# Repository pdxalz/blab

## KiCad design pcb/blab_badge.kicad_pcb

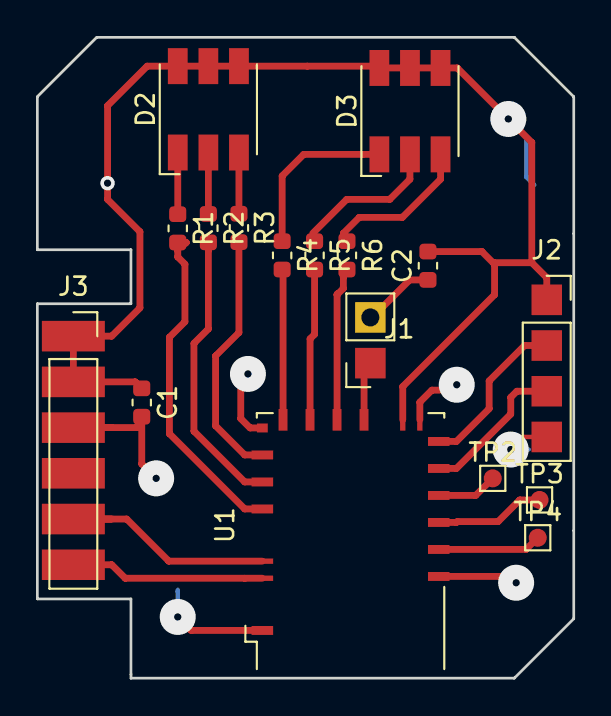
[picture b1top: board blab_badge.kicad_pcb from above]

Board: 2 copper layers, 29.8 x 35.6 mm, 18 parts (1 on the bottom side), 22 nets.

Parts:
BT1: Battery_Cell; BatteryHolder_MPD_BC2003_1x2032
C1, C2: C; C_0603_1608Metric
D2, D3: LED_RGB_5050; LED_RGB_5050-6
J1: Conn_01x02; PinSocket_1x02_P2.54mm_Vertical
J2: Conn_01x04; PinSocket_1x04_P2.54mm_Vertical
J3: Conn_01x06; PinSocket_1x06_P2.54mm_Vertical
R1, R2, R3, R4, R5, R6: 330; R_0603_1608Metric
TP2, TP3, TP4: TestPoint; TestPoint_Pad_1.0x1.0mm
U1: az_BL652; Laird_BL652

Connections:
+3V3: BT1.1, C1.1, C2.2, D2.4, D2.5, D2.6, D3.4, D3.5, D3.6, J2.1, J3.1, J3.2, U1.26
BLUE0: R3.2, U1.14
BLUE1: R6.2, U1.21
CTS: TP4.1, U1.37
GND: BT1.2, C1.2, C2.1, J1.2, J2.4, J3.3, U1.1, U1.16, U1.27, U1.39
GREEN0: R1.2, U1.10
GREEN1: R4.2, U1.17
unnamed: D2.1, R1.1
unnamed: D2.2, R2.1
unnamed: D2.3, R3.1
unnamed: D3.1, R4.1
unnamed: D3.2, R5.1
unnamed: D3.3, R6.1
unnamed: J3.5, U1.6
unnamed: J3.6, U1.5
unnamed: TP2.1, U1.33
RED0: R2.2, U1.12
RED1: R5.2, U1.19
RTS: TP3.1, U1.35
RX: J2.2, U1.29
SW0: J1.1, U1.23
TX: J2.3, U1.31

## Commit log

2024-12-27 updated .gitignore
2024-12-27 Added timeouts for talking and blinking LEDs
2024-12-27 Stop tracking build directory
2024-12-28 fixed how talking minutes are counted. Player with least minutes talks next.
2024-12-28 kludge fix for bad gpio on one board.
2024-12-29 Cleaned up code, set longer timeout constants.
2024-12-29 Added badge pcb design files
2024-12-29 Added 3D print .obj files
2025-01-02 Increased delay before a second click is allowed
